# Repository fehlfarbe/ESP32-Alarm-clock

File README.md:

# ESP32 Alarm clock

This is an ESP32 based alarm clock that plays mp3 files from SD, webstreams or even FM radio.
You can configure multiple alarms and add new songs to your sd card with a simple webinterface.

Photos of the current PCB version (without assembled radio antenna connector J10):

## Features

- designed for ESP32 S3 microcontroller
- plays audio from different sources:
  - MP3/AAC from SD
  - webstreams via WiFi
  - FM radio via [RDA5807FP](https://opendevices.ru/wp-content/uploads/2015/10/RDA5807FP.pdf) module
- output via I2S to a stereo decoder like the [UDA1334A](https://learn.adafruit.com/adafruit-i2s-stereo-decoder-uda1334a).
- see current time on TM1637 4-Digit Digital LED display
- see current WiFi state with WS2812 RGB LED
- simple config and file upload via webinterface

## Hardware

The KiCAD project and gerber files are available at `hardware/pcb/`

### Schematic

### 2D Plot

#### Front

#### Back

### 3D Render

#### Front

#### Back

### BOM

`hardware/pcb/export/BOM.xml`

## LED States

### Status LED

-  1Hz blinking: An Error has occurred while mounting LITTLEFS
-  0.5Hz blinking: Cannot mount SD card
-  Everything is fine :)

### WiFi LED

-   AccessPoint mode: Connect to the ESP's access point and configure your WiFi
-  ... WiFi signal strength from bad to good

## Installation

Just clone the project and open it in platformIO. PIO will download all necessary libs. Connect the ESP32 on your USB port an click "Upload" in PIO. After this open a terminal in PIO and run `pio run -t uploadfs` to upload the webinterface to ESP32's flash.
The ESP32 will reboot and opens an accesspoint where you can connect to your WiFi. The clock is synced over the internet via NTP.

## ToDo

- [ ] Add alarm timeout (for webstreams, radio etc.)
- [ ] better web UI based on react
- [x] pictures of full assembled board
- [ ] complete BOM list

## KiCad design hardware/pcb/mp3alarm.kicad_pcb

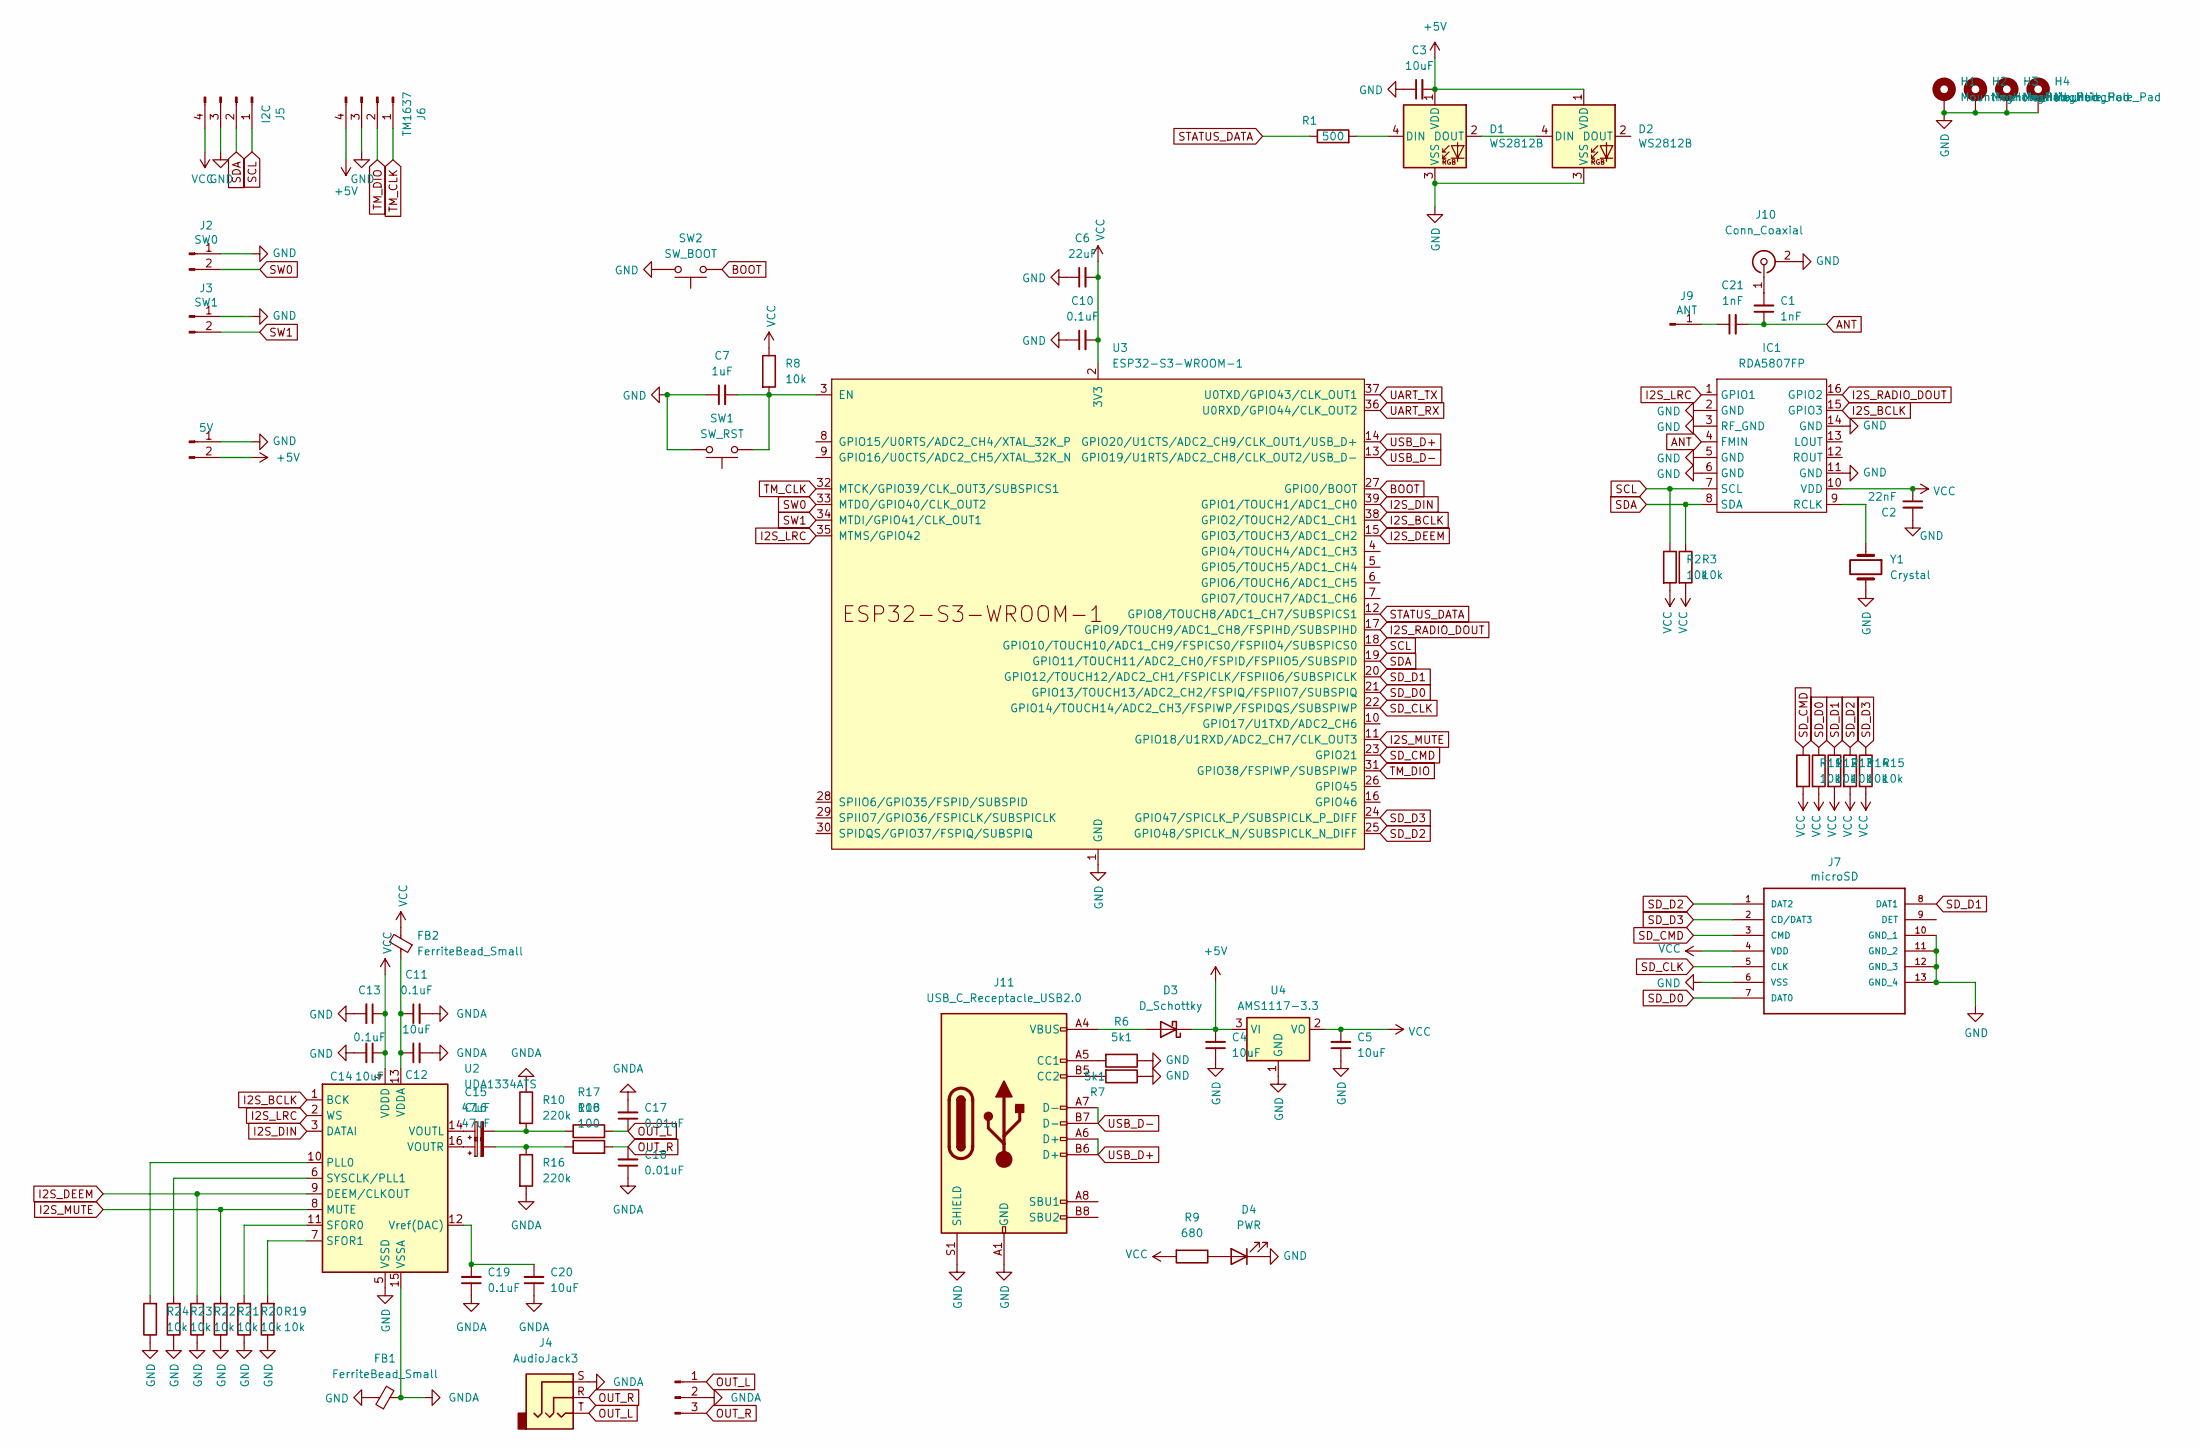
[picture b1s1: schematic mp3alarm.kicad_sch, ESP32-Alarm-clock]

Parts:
C1, C21: 1nF; C_1206_3216Metric
C2: 22nF; C_1206_3216Metric
C3, C4, C5, C12, C14, C20: 10uF; C_1206_3216Metric
C6: 22uF; C_1206_3216Metric
C7: 1uF; C_1206_3216Metric
C10, C11, C13, C19: 0.1uF; C_1206_3216Metric
C15, C16: 47uF; C_Elec_6.3x5.4
C17, C18: 0.01uF; C_1206_3216Metric
D1, D2: WS2812B; LED_WS2812B_PLCC4_5.0x5.0mm_P3.2mm
D3: D_Schottky; D_0805_2012Metric
D4: PWR; LED_0805_2012Metric
FB1, FB2: FerriteBead_Small; R_0805_2012Metric
H1, H2, H3, H4: MountingHole_Pad; MountingHole_3.2mm_M3_Pad
IC1: RDA5807FP; SOP-16_3.9x9.9mm_P1.27mm
J1: AUDIO; PinHeader_1x03_P2.54mm_Vertical
J2: SW0; PinHeader_1x02_P2.54mm_Vertical
J3: SW1; PinHeader_1x02_P2.54mm_Vertical
J4: AudioJack3; PJ-313
J5: I2C; PinHeader_1x04_P2.54mm_Vertical
J6: TM1637; PinHeader_1x04_P2.54mm_Vertical
J7: microSD; 105162-0001; MOUSER_PART_NUMBER 538-105162-0001
J8: 5V; PinHeader_1x02_P2.54mm_Vertical
J9: ANT; PinHeader_1x01_P2.54mm_Vertical
J10: Conn_Coaxial; F_Sat_Connector
J11: USB_C_Receptacle_USB2.0; USB_C_Receptacle_JAE_DX07S016JA1R1500
R1: 500; R_1206_3216Metric
R2, R3, R8, R11, R12, R13, R14, R15, R19, R20, R21, R22, R23, R24: 10k; R_1206_3216Metric
R6, R7: 5k1; R_1206_3216Metric
R9: 680; R_1206_3216Metric
R10, R16: 220k; R_1206_3216Metric
R17, R18: 100; R_1206_3216Metric
SW1: SW_RST; SW_SPST_CK_RS282G05A3
SW2: SW_BOOT; SW_SPST_CK_RS282G05A3
U2: UDA1334ATS; SSOP-16_4.4x5.2mm_P0.65mm
U3: ESP32-S3-WROOM-1
U4: AMS1117-3.3; SOT-223-3_TabPin2
Y1: Crystal; Crystal_SMD_2012-2Pin_2.0x1.2mm

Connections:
+5V: C3.2, C4.2, D1.1 (VDD), D2.1 (VDD), D3.1 (K), J6.4, J8.2, U4.3 (VI)
ANT: C1.1, C21.2, IC1.4 (FMIN)
BOOT: SW2.1, U3.27 (GPIO0/BOOT)
GND: C2.2, C3.1, C4.1, C5.1, C6.1, C7.1, C10.1, C13.2, C14.2, D1.3 (VSS), D2.3 (VSS), D4.1 (K), FB1.1, H1.1, H2.1, H3.1, H4.1, IC1.2 (GND), IC1.3 (RF_GND), IC1.5 (GND), IC1.6 (GND), IC1.11 (GND), IC1.14 (GND), J2.1, J3.1, J5.3, J6.3, J7.6 (VSS), J7.10 (GND_1), J7.11 (GND_2), J7.12 (GND_3), J7.13 (GND_4), J8.1, J10.2 (Ext), J11.A1 (GND), J11.A12 (GND), J11.B1 (GND), J11.B12 (GND), J11.S1 (SHIELD), R6.1, R7.1, R19.1, R20.1, R21.1, R22.1, R23.1, R24.1, SW1.2, SW2.2, U2.5 (VSSD), U3.1 (GND), U3.40 (GND), U3.41 (GND), U4.1 (GND), Y1.2
GNDA: C11.2, C12.2, C17.2, C18.1, C19.1, C20.1, FB1.2, J1.2, J4.S, R10.1, R16.2, U2.15 (VSSA)
I2S_BCLK: IC1.15 (GPIO3), U2.1 (BCK), U3.38 (GPIO2/TOUCH2/ADC1_CH1)
I2S_DEEM: R22.2, U2.9 (DEEM/CLKOUT), U3.15 (GPIO3/TOUCH3/ADC1_CH2)
I2S_DIN: U2.3 (DATAI), U3.39 (GPIO1/TOUCH1/ADC1_CH0)
I2S_LRC: IC1.1 (GPIO1), U2.2 (WS), U3.35 (MTMS/GPIO42)
I2S_MUTE: R21.2, U2.8 (MUTE), U3.11 (GPIO18/U1RXD/ADC2_CH7/CLK_OUT3)
I2S_RADIO_DOUT: IC1.16 (GPIO2), U3.17 (GPIO9/TOUCH9/ADC1_CH8/FSPIHD/SUBSPIHD)
unnamed: C15.2, R10.2, R17.1
unnamed: C16.2, R16.1, R18.1
unnamed: D1.4 (DIN), R1.2
unnamed: D1.2 (DOUT), D2.4 (DIN)
unnamed: D3.2 (A), J11.A4 (VBUS), J11.A9 (VBUS), J11.B4 (VBUS), J11.B9 (VBUS)
unnamed: D4.2 (A), R9.1
unnamed: IC1.9 (RCLK), Y1.1
unnamed: C21.1, J9.1
unnamed: C1.2, J10.1 (In)
unnamed: J11.A5 (CC1), R6.2
unnamed: J11.B5 (CC2), R7.2
unnamed: R24.2, U2.10 (PLL0)
unnamed: R20.2, U2.11 (SFOR0)
unnamed: R19.2, U2.7 (SFOR1)
unnamed: R23.2, U2.6 (SYSCLK/PLL1)
unnamed: C11.1, C12.1, FB2.1, U2.13 (VDDA)
unnamed: C15.1, U2.14 (VOUTL)
unnamed: C16.1, U2.16 (VOUTR)
unnamed: C19.2, C20.2, U2.12 (Vref(DAC))
unnamed: C7.2, R8.2, SW1.1, U3.3 (EN)
OUT_L: C17.1, J1.1, J4.T, R17.2
OUT_R: C18.2, J1.3, J4.R, R18.2
SCL: IC1.7 (SCL), J5.1, R2.1, U3.18 (GPIO10/TOUCH10/ADC1_CH9/FSPICS0/FSPIIO4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)
SDA: IC1.8 (SDA), J5.2, R3.1, U3.19 (GPIO11/TOUCH11/ADC2_CH0/FSPID/FSPIIO5/S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)
SD_CLK: J7.5 (CLK), U3.22 (GPIO14/TOUCH14/ADC2_CH3/FSPIWP/FSPIDQS/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)
SD_CMD: J7.3 (CMD), R11.1, U3.23 (GPIO21)
SD_D0: J7.7 (DAT0), R12.1, U3.21 (GPIO13/TOUCH13/ADC2_CH2/FSPIQ/FSPIIO7/S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)
SD_D1: J7.8 (DAT1), R13.1, U3.20 (GPIO12/TOUCH12/ADC2_CH1/FSPICLK/FSPIIO6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)
SD_D2: J7.1 (DAT2), R14.1, U3.25 (GPIO48/SPICLK_N/SUBSPICLK_N_DIFF)
SD_D3: J7.2 (CD/DAT3), R15.1, U3.24 (GPIO47/SPICLK_P/SUBSPICLK_P_DIFF)
STATUS_DATA: R1.1, U3.12 (GPIO8/TOUCH8/ADC1_CH7/SUBSPICS1)
SW0: J2.2, U3.33 (MTDO/GPIO40/CLK_OUT2)
SW1: J3.2, U3.34 (MTDI/GPIO41/CLK_OUT1)
TM_CLK: J6.1, U3.32 (MTCK/GPIO39/CLK_OUT3/SUBSPICS1)
TM_DIO: J6.2, U3.31 (GPIO38/FSPIWP/SUBSPIWP)
UART_RX: U3.36 (U0RXD/GPIO44/CLK_OUT2)
UART_TX: U3.37 (U0TXD/GPIO43/CLK_OUT1)
USB_D+: J11.A6 (D+), J11.B6 (D+), U3.14 (GPIO20/U1CTS/ADC2_CH9/CLK_OUT1/USB_D+)
USB_D-: J11.A7 (D-), J11.B7 (D-), U3.13 (GPIO19/U1RTS/ADC2_CH8/CLK_OUT2/USB_D-)
VCC: C2.1, C5.2, C6.2, C10.2, C13.1, C14.1, FB2.2, IC1.10 (VDD), J5.4, J7.4 (VDD), R2.2, R3.2, R8.1, R9.2, R11.2, R12.2, R13.2, R14.2, R15.2, U2.4 (VDDD), U3.2 (3V3), U4.2 (VO)

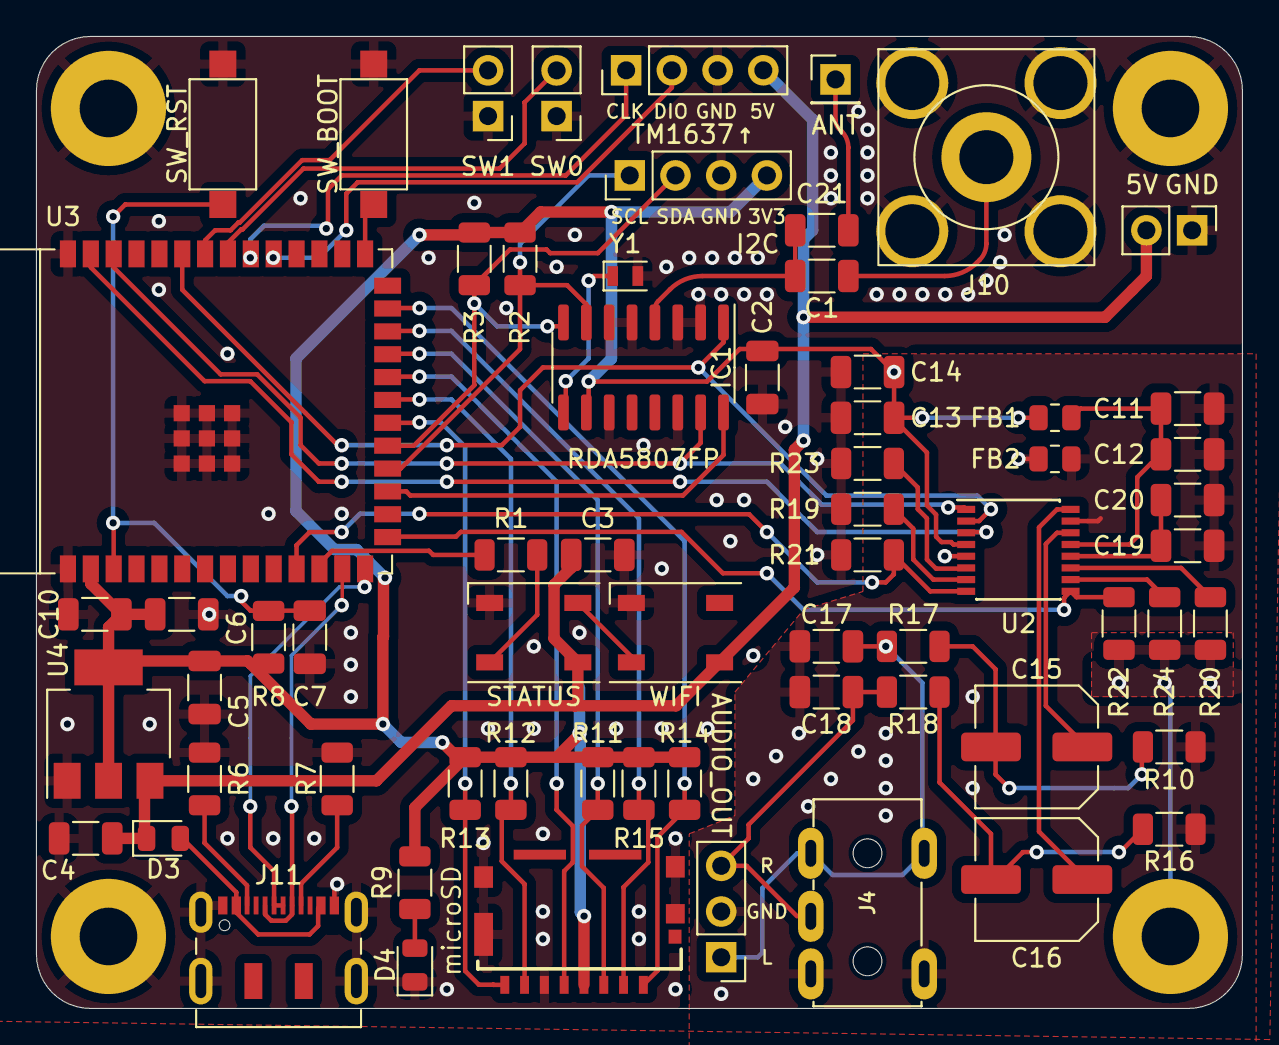
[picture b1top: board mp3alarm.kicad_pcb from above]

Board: 2 copper layers, 67.0 x 54.0 mm, 69 parts (0 on the bottom side), 49 nets.

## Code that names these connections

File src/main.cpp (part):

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
// Digital I/O used
#define I2S_DOUT 1
#define I2S_BCLK 2
#define I2S_WS 42
#define I2S_RADIO_OUT 9
#define I2S_MUTE 18
#define I2S_DEEM 3

// SD_MMC
#define SD_MMC_CLK 14
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    // setup pins
    pinMode(SW0, INPUT_PULLUP);
    pinMode(SW1, INPUT_PULLUP);
    pinMode(I2S_MUTE, OUTPUT);
    pinMode(I2S_DEEM, OUTPUT);

    // setup LEDs
    FastLED.addLeds<NEOPIXEL, LED_STATUS>(led_status, 2);
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
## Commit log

2020-09-02 Most features should work now
2020-09-02 Added README
2020-09-03 Added new configs for webinterface
2020-09-04 File upload working :)
2020-09-06 Changed pins for final board, cleanup, get board infos via http
2020-09-13 Added 7 segment display and simple pcb
2020-09-27 small changes
2020-10-27 bugfixes, added language support, timezone/dst
2020-10-29 Added OTA update
2020-11-19 - Added FM radio - refactoring: moved streaming etc. to MusicStream - ToDo: I2S Radio input lib not working yet
2020-11-19 Added FM stuff / bugfixes
2020-11-20 Bugfixing
2020-12-22 KiCAD PCB Webinterface bugfixes
2021-01-07 FM module working
2021-01-11 Updated PCB (added QR code, OSHW logo, etc) Some bugfixes for webinterface Updated README
2023-01-08 New PCB with RDA5807FP
2023-01-31 * New partition table * Changed to audio pipeline (arduino-audio-tools) * PCB: new sat connector layout * PCB: added pullup resistors for switch pins
2023-04-07 Working stream, file and radio
2023-04-19 Mp3 playback without stuttering and volume control for I2S radio
2023-05-10 * Added new options for static network settings * Improved firmware update via HTTP (update firmware and filesystem) * several bugfixes
2023-05-15 Enabled HTTP caching for static files and disabled cyclic playback request that caused stuttering on playback
2023-05-16 README
2023-05-16 PCB updates
2023-05-16 * Added display again * Don't change audio volume on config load
2023-05-16 README updates
2023-05-22 Fixed deleting files via webcontrol
2023-06-06 * Fixed file playback for alarm * Fixed alarm volume scale at webcontrol
2023-07-26 * Playback volume bugfix * Added hardware button to stop playback * small bugfixes
2023-11-14 Ported project to ESP32S3 with SD_MMC support and pinned AsyncTCP task to core0 to prevent stuttering
2023-12-08 Several bugfixes and reactoring: * If there is no config on startup, a default config.json, streams.json and songs directory will be created * Fixed bugs for file upload * Webinterface shows file siz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
2023-12-08 * Removed unnecessary delay on start * Forced AP mode deletes WiFi config so it stays in AP mode * Broken alarms fixed * File upload returns the right file size instead 0
2023-12-08 * Latest PCB update for ESP32S3
2023-12-08 Updated .gitignore
2023-12-09 Updated to latest PCB
2023-12-26 Changed WiFi/System LED status handling Removed Caching for static files
2023-12-26 Added loading spinner to web interface
2024-01-11 * Updated audio pipeline libs * Webinterface: load songs first, then config to prevent not found songs in config * prevent JSON parsing errors for some webstream URLs * Increased buffer size for bett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
2024-01-11 * Yellow status LED if time cannot be synced * Fixed bug that selected a wrong following alarm
2024-03-11 Updated PCB
2024-03-11 Refactored Settings/Alarm structure and added timezone selection to web interface
2024-03-11 Alarms can now be disabled in web interface
2024-04-16 * Updated ArduinoJSON code * TM1637Display shows more errors
2024-04-20 Show red color if WiFi RSSI is 0 instead of pure green
2024-04-20 Pin ArduinoJSON version to 7.0.4
2024-04-20 Latest PCB update
2024-04-20 Added new photos to README
2024-06-03 Added React webinterface with some simple unfinished components
2024-09-11 Added React and websocket based web interface with audio player (config site still in progress)
2024-11-13 Bugfix: get/set audio volume in webconfig
2024-11-13 Bugfix: map selected alarm audio to audio sources in web control
2024-12-04 Added support for separate volume for every alarm
2024-12-04 Code formatting
2025-01-02 Playing audio from web interface with default audio volume from settings
2025-11-04 Updated libs and memory layout for ESP32-S3 N16-R2
2025-11-21 Updated libs
2025-11-21 New partition layout
2025-12-10 Fix error message on file upload due to wrong http response
2025-12-10 Fix for not starting config portal
2025-12-11 Use current volume when playing audio instead of general volume setting
2025-12-11 Updated audio tools and mp3decoder
2025-12-11 Added simple firmware build/erxport script
